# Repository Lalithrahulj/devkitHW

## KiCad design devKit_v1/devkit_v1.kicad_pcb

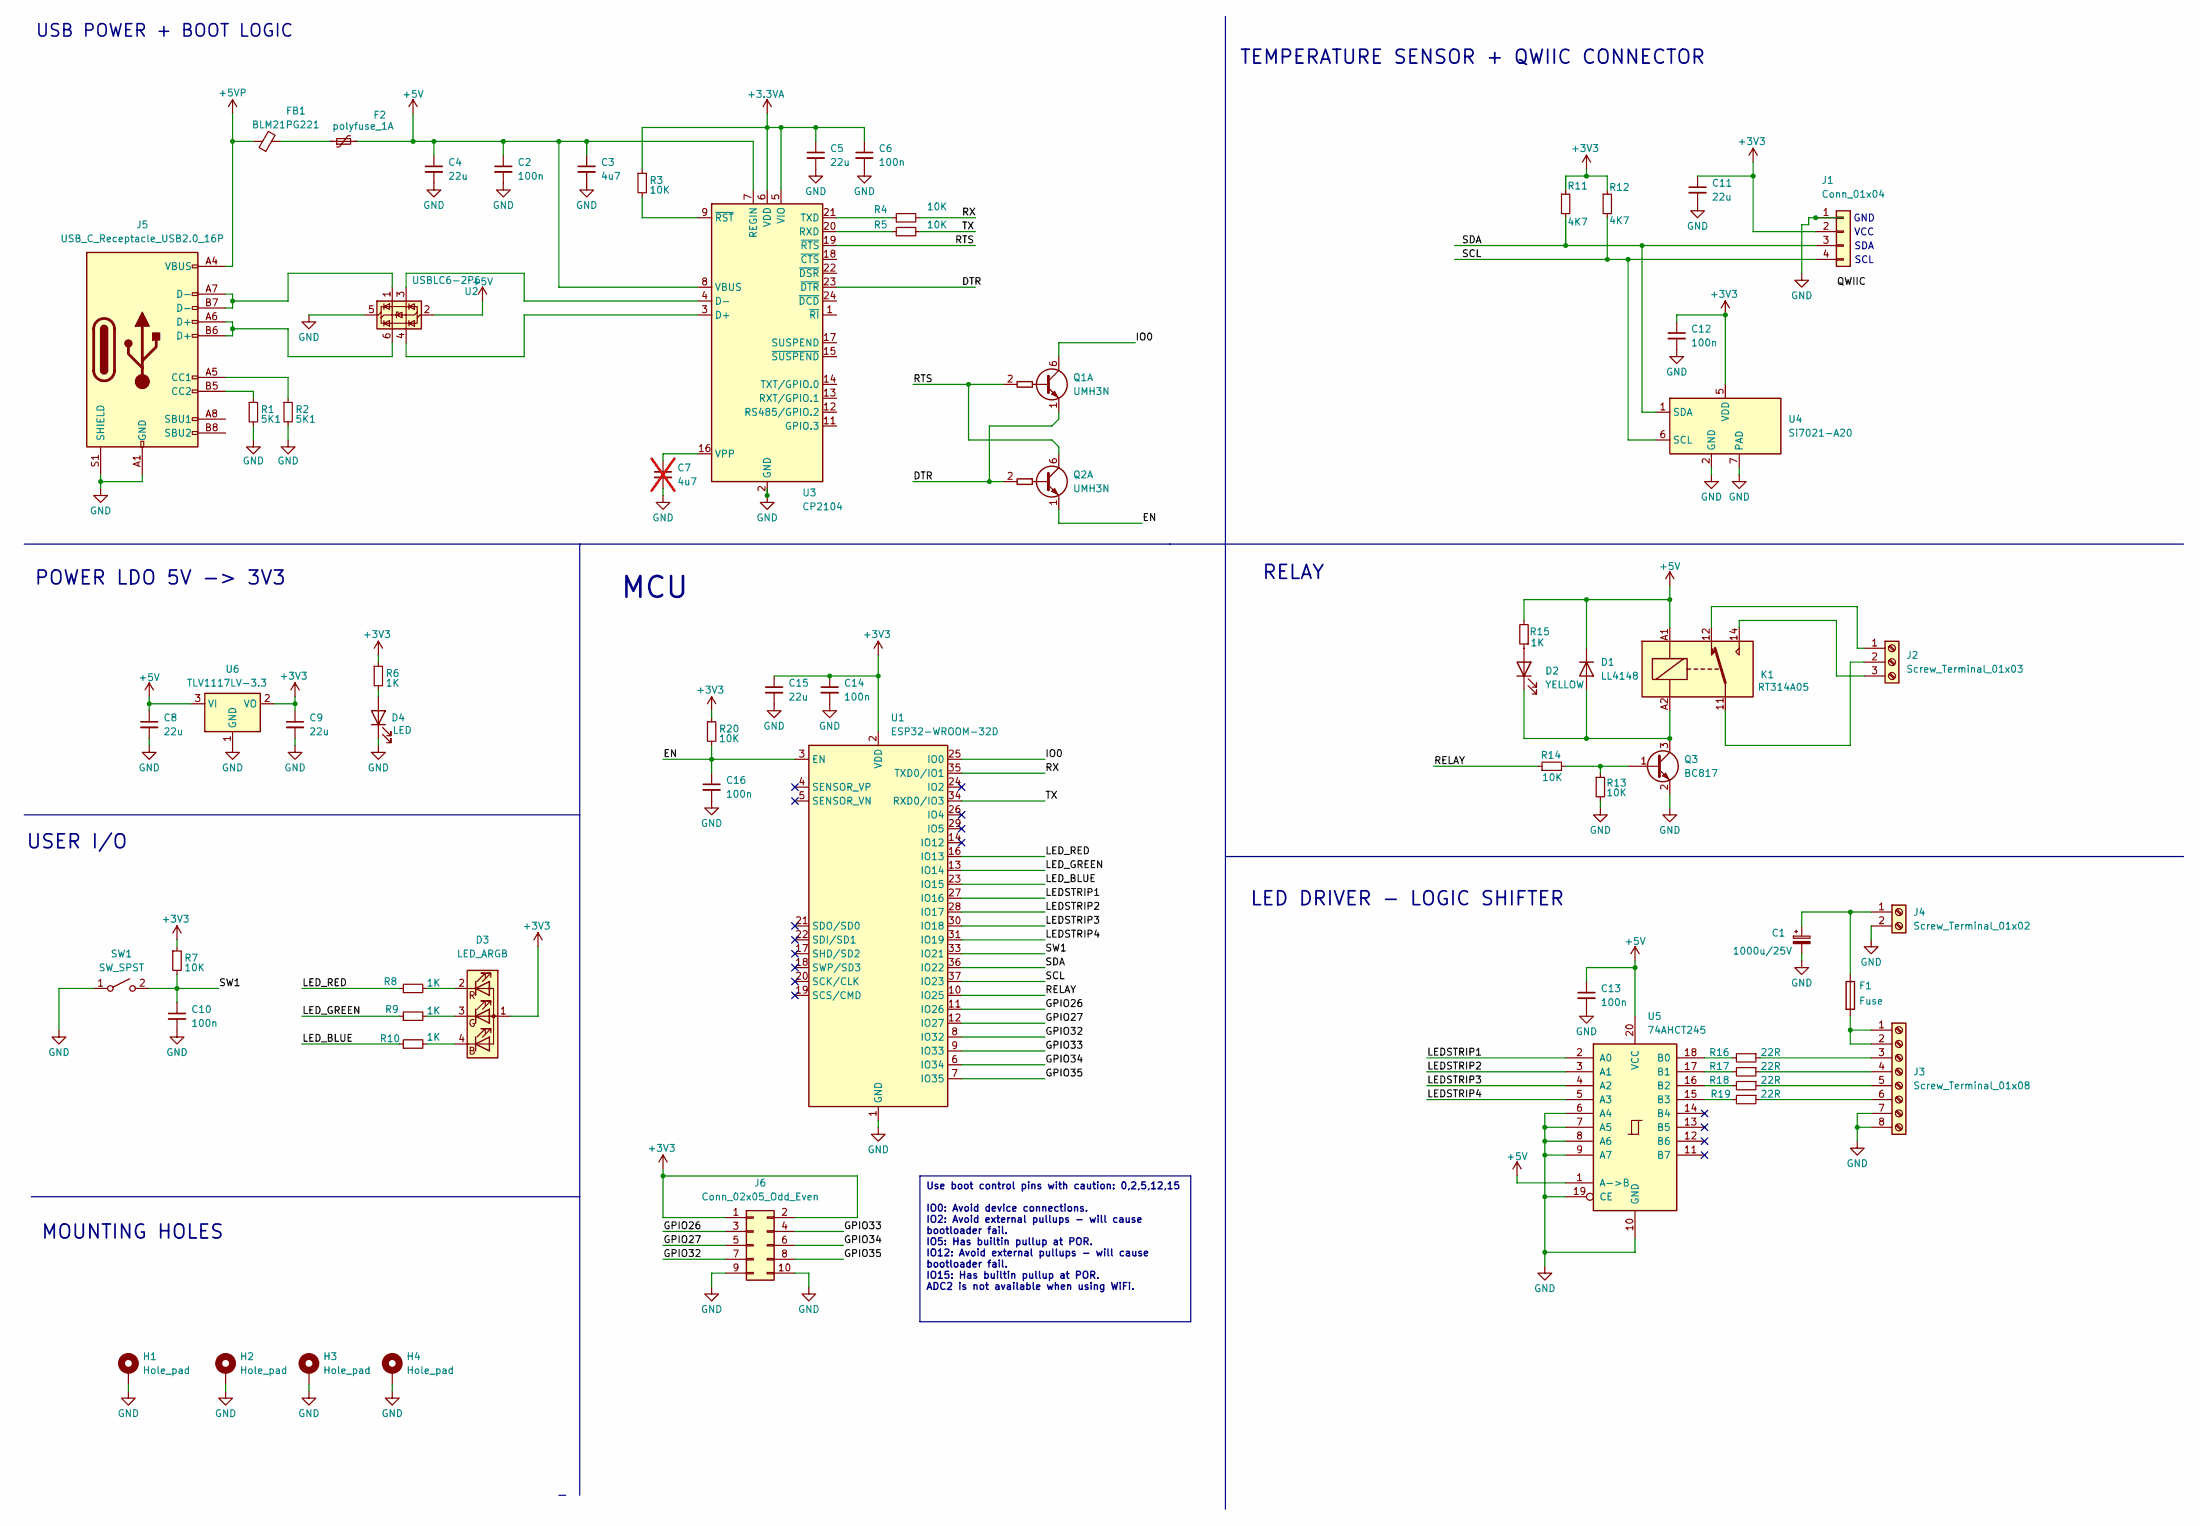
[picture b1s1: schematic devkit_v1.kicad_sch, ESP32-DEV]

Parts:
C1: 1000u/25V; CP_Radial_D10.0mm_P5.00mm
C2, C6, C10, C12, C13, C14, C16: 100n; C_0402_1005Metric_Pad0.74x0.62mm_HandSolder
C3: 4u7; C_0805_2012Metric_Pad1.18x1.45mm_HandSolder
C4, C5, C8, C9, C11, C15: 22u; C_0805_2012Metric_Pad1.18x1.45mm_HandSolder
C7: 4u7; C_0805_2012Metric_Pad1.18x1.45mm_HandSolder; not fitted
D1: LL4148; D_MiniMELF
D2: YELLOW; LED_0603_1608Metric_Pad1.05x0.95mm_HandSolder
D3: LED_ARGB; LED_RGB_Wuerth-PLCC4_3.2x2.8mm_150141M173100
D4: LED; LED_0603_1608Metric_Pad1.05x0.95mm_HandSolder
F1: Fuse; Fuseholder_Cylinder-5x20mm_Wuerth_696103101002-SMD_Horizont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
F2: polyfuse_1A; Fuse_1206_3216Metric_Pad1.42x1.75mm_HandSolder
FB1: BLM21PG221; L_0603_1608Metric_Pad1.05x0.95mm_HandSolder
H1, H2, H3, H4: Hole_pad; MountingHole_3.2mm_M3_Pad_Via
J1: Conn_01x04; JST_SH_SM04B-SRSS-TB_1x04-1MP_P1.00mm_Horizontal
J2: Screw_Terminal_01x03; TerminalBlock_Phoenix_MKDS-3-3-5.08_1x03_P5.08mm_Horizontal
J3: Screw_Terminal_01x08; TerminalBlock_Phoenix_MKDS-1,5-8_1x08_P5.00mm_Horizontal
J4: Screw_Terminal_01x02; TerminalBlock_Phoenix_MKDS-1,5-2-5.08_1x02_P5.08mm_Horizont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
J5: USB_C_Receptacle_USB2.0_16P; USB_C_Receptacle_HRO_TYPE-C-31-M-12
J6: Conn_02x05_Odd_Even; PinHeader_2x05_P2.54mm_Vertical
K1: RT314A05; Relay_SPDT_Schrack-RT1-16A-FormC_RM5mm
Q1, Q2: UMH3N; SOT-363_SC-70-6
Q3: BC817; SOT-23
R1, R2: 5K1; R_0402_1005Metric_Pad0.72x0.64mm_HandSolder
R3, R4, R5, R7, R13, R14, R20: 10K; R_0402_1005Metric_Pad0.72x0.64mm_HandSolder
R6, R8, R9, R10, R15: 1K; R_0402_1005Metric_Pad0.72x0.64mm_HandSolder
R11, R12: 4K7; R_0402_1005Metric_Pad0.72x0.64mm_HandSolder
R16, R17, R18, R19: 22R; R_0402_1005Metric_Pad0.72x0.64mm_HandSolder
SW1: SW_SPST; SW_Push_1P1T_NO_CK_KMR2
U1: ESP32-WROOM-32D
U2: USBLC6-2P6; SOT-666
U3: CP2104; QFN-24-1EP_4x4mm_P0.5mm_EP2.6x2.6mm
U4: Si7021-A20; DFN-6-1EP_3x3mm_P1mm_EP1.5x2.4mm
U5: 74AHCT245; DIP-20_W7.62mm
U6: TLV1117LV-3.3; SOT-223-3_TabPin2

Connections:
+3.3VA: C5.1, C6.1, R3.1, U3.5 (VIO), U3.6 (VDD)
+3V3: C9.1, C11.1, C12.1, C14.1, C15.1, D3.1 (A), J1.2, J6.1, J6.2, R6.1, R7.1, R11.1, R12.1, R20.1, U1.2 (VDD), U4.5 (VDD), U6.2 (VO)
+5V: C2.1, C3.1, C4.1, C8.1, C13.1, D1.1 (K), F2.2, K1.A1, R15.2, U2.2 (GND), U3.7 (REGIN), U3.8 (VBUS), U5.1 (A->B), U5.20 (VCC), U6.3 (VI)
+5VP: FB1.1, J5.A4 (VBUS), J5.A9 (VBUS), J5.B4 (VBUS), J5.B9 (VBUS)
/DTR: Q1.1 (E1), Q2.2 (B1), U3.23 (~DTR)
/EN: C16.1, Q2.1 (E1), R20.2, U1.3 (EN)
/GPIO26: J6.3, U1.11 (IO26)
/GPIO27: J6.5, U1.12 (IO27)
/GPIO32: J6.7, U1.8 (IO32)
/GPIO33: J6.4, U1.9 (IO33)
/GPIO34: J6.6, U1.6 (IO34)
/GPIO35: J6.8, U1.7 (IO35)
/IO0: Q1.6 (C1), U1.25 (IO0)
/LEDSTRIP1: U1.27 (IO16), U5.2 (A0)
/LEDSTRIP2: U1.28 (IO17), U5.3 (A1)
/LEDSTRIP3: U1.30 (IO18), U5.4 (A2)
/LEDSTRIP4: U1.31 (IO19), U5.5 (A3)
/LED_BLUE: R10.1, U1.23 (IO15)
/LED_GREEN: R9.1, U1.13 (IO14)
/LED_RED: R8.1, U1.16 (IO13)
/RELAY: R14.1, U1.10 (IO25)
/RTS: Q1.2 (B1), Q2.6 (C1), U3.19 (~RTS)
/RX: R4.2, U1.35 (TXD0/IO1)
/SCL: J1.4, R12.2, U1.37 (IO23), U4.6 (SCL)
/SDA: J1.3, R11.2, U1.36 (IO22), U4.1 (SDA)
/SW1: C10.1, R7.2, SW1.2 (B), U1.33 (IO21)
/TX: R5.2, U1.34 (RXD0/IO3)
GND: C1.2, C2.2, C3.2, C4.2, C5.2, C6.2, C7.2, C8.2, C9.2, C10.2, C11.2, C12.2, C13.2, C14.2, C15.2, C16.2, D4.1 (K), H1.1, H2.1, H3.1, H4.1, J1.1, J3.7, J3.8, J4.2, J5.A1 (GND), J5.A12 (GND), J5.B1 (GND), J5.B12 (GND), J5.S1 (SHIELD), J6.9, J6.10, Q3.2 (E), R1.2, R2.2, R13.2, SW1.1 (A), U1.1 (GND), U1.15 (GND), U1.38 (GND), U1.39 (GND), U2.5 (VBUS), U3.2 (GND), U3.25 (GND), U4.2 (GND), U4.7 (PAD), U5.6 (A4), U5.7 (A5), U5.8 (A6), U5.9 (A7), U5.10 (GND), U5.19 (CE), U6.1 (GND)
unnamed: D1.2 (A), D2.1 (K), K1.A2, Q3.3 (C)
unnamed: D2.2 (A), R15.1
unnamed: D3.4 (BK), R10.2
unnamed: D3.3 (GK), R9.2
unnamed: D3.2 (RK), R8.2
unnamed: D4.2 (A), R6.2
unnamed: F2.1, FB1.2
unnamed: J2.1, K1.12
unnamed: J2.2, K1.11
unnamed: J2.3, K1.14
unnamed: F1.2, J3.1, J3.2
unnamed: J3.3, R16.1
unnamed: J3.4, R17.1
unnamed: J3.5, R18.1
unnamed: J3.6, R19.1
unnamed: C1.1, F1.1, J4.1
unnamed: J5.A5 (CC1), R2.1
unnamed: J5.B5 (CC2), R1.1
unnamed: J5.A6 (D+), J5.B6 (D+), U2.6 (I/O1)
unnamed: J5.A7 (D-), J5.B7 (D-), U2.1 (I/O1)
unnamed: Q3.1 (B), R13.1, R14.2
unnamed: U2.4 (I/O2), U3.3 (D+)
unnamed: U2.3 (I/O2), U3.4 (D-)
unnamed: R5.1, U3.20 (RXD)
unnamed: R4.1, U3.21 (TXD)
unnamed: C7.1, U3.16 (VPP)
unnamed: R3.2, U3.9 (~RST)
unnamed: R16.2, U5.18 (B0)
unnamed: R17.2, U5.17 (B1)
unnamed: R18.2, U5.16 (B2)
unnamed: R19.2, U5.15 (B3)

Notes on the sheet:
Use boot control pins with caution: 0,2,5,12,15 IO0: Avoid device connections. IO2: Avoid external pullups - will cause bootloader fail. IO5: Has builtin pullup at POR. IO12: Avoid external pullups - will cause bootloader fail. IO15: Has builtin pullup at POR. ADC2 is not available when using WiFi.
USER I/O
RELAY
MOUNTING HOLES
MCU
LED DRIVER - LOGIC SHIFTER
SDA
TEMPERATURE SENSOR + QWIIC CONNECTOR
VCC
SCL
USB POWER + BOOT LOGIC
POWER LDO 5V -> 3V3
GND

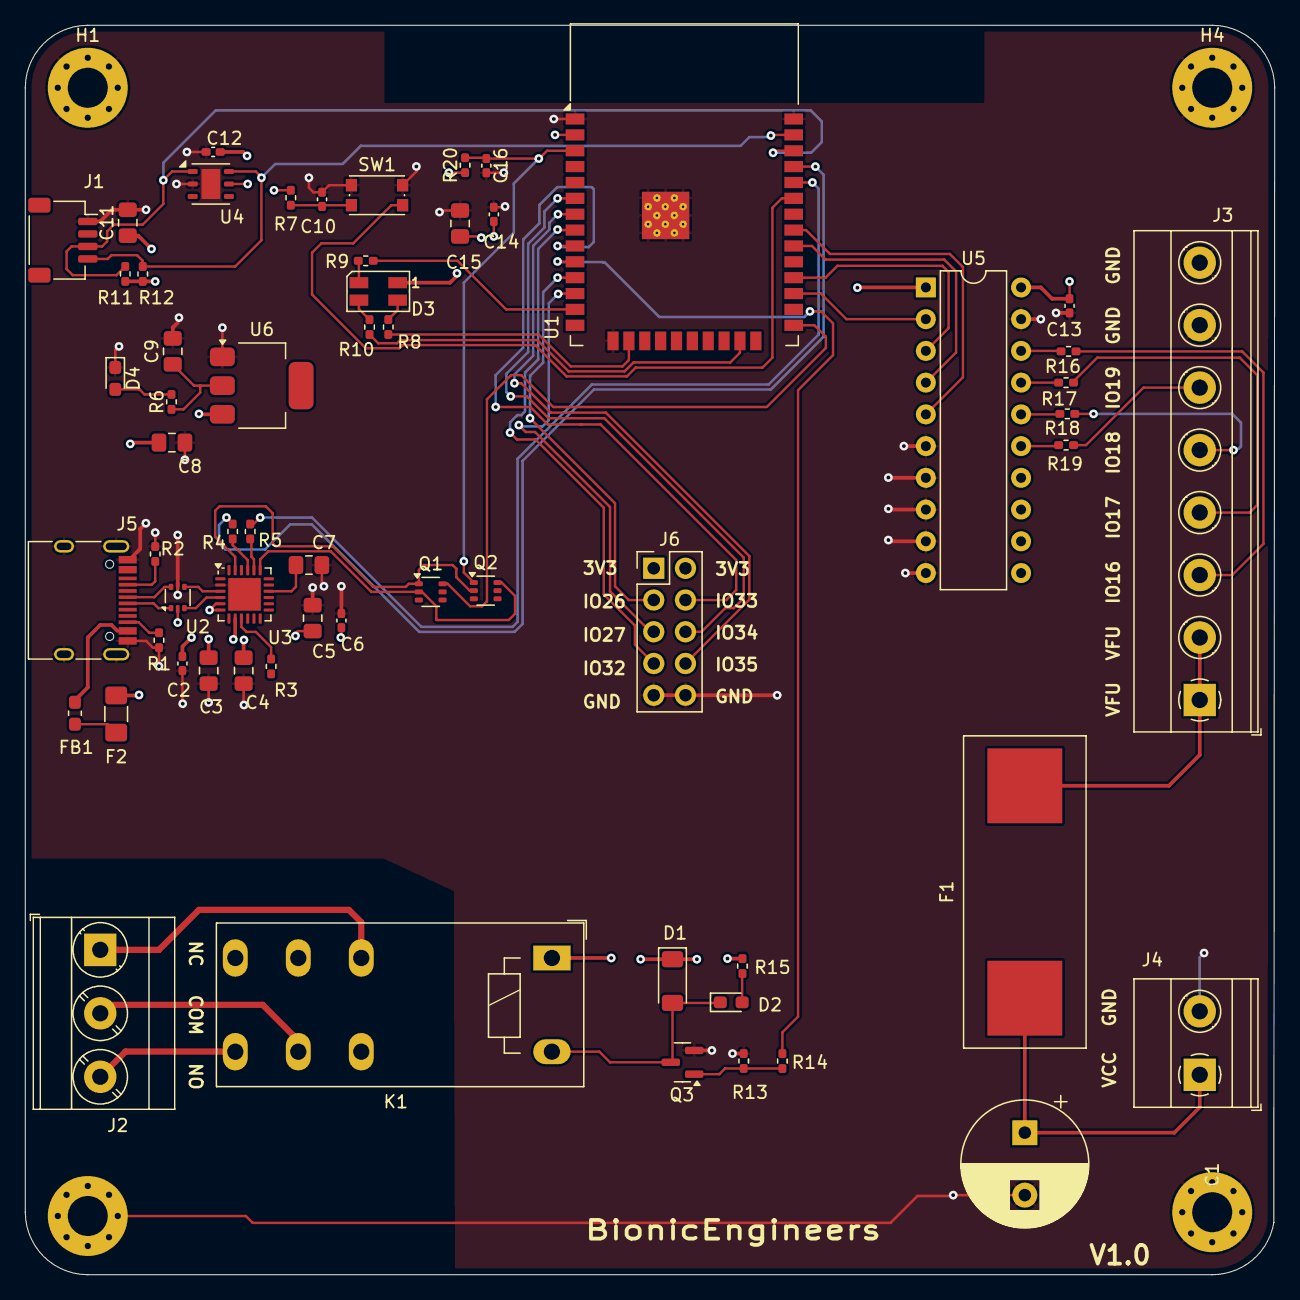
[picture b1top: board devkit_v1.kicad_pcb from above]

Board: 4 copper layers, 100.0 x 100.0 mm, 64 parts (0 on the bottom side), 59 nets.

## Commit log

2024-12-29 Adding the devkit project files
